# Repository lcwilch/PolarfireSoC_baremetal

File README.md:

# PolarfireSoC_baremetal
Projects for learing Microchip Polarfire SoC using the BeagleV-Fire SBC.
https://www.microchip.com/en-us/products/fpgas-and-plds/system-on-chip-fpgas/polarfire-soc-fpgas
https://www.beagleboard.org/boards/beaglev-fire

# Docs:
MPFS, RISCV documents

# KiCad:
Any PCBs needed to support development (i.e. J-Link to Flashpro JTAG pinout adapter)

# Libero:
MSS Configurator and Libero Projects for configuring MPFS HW

# Schematics:
BeagleV-Fire schematic

# Source:
ESW projects targeting various functionality of the MPFS using U54 core complex

# Debug
Debug utilities, like openocd and fpserver for debuging MPFS with flashpro

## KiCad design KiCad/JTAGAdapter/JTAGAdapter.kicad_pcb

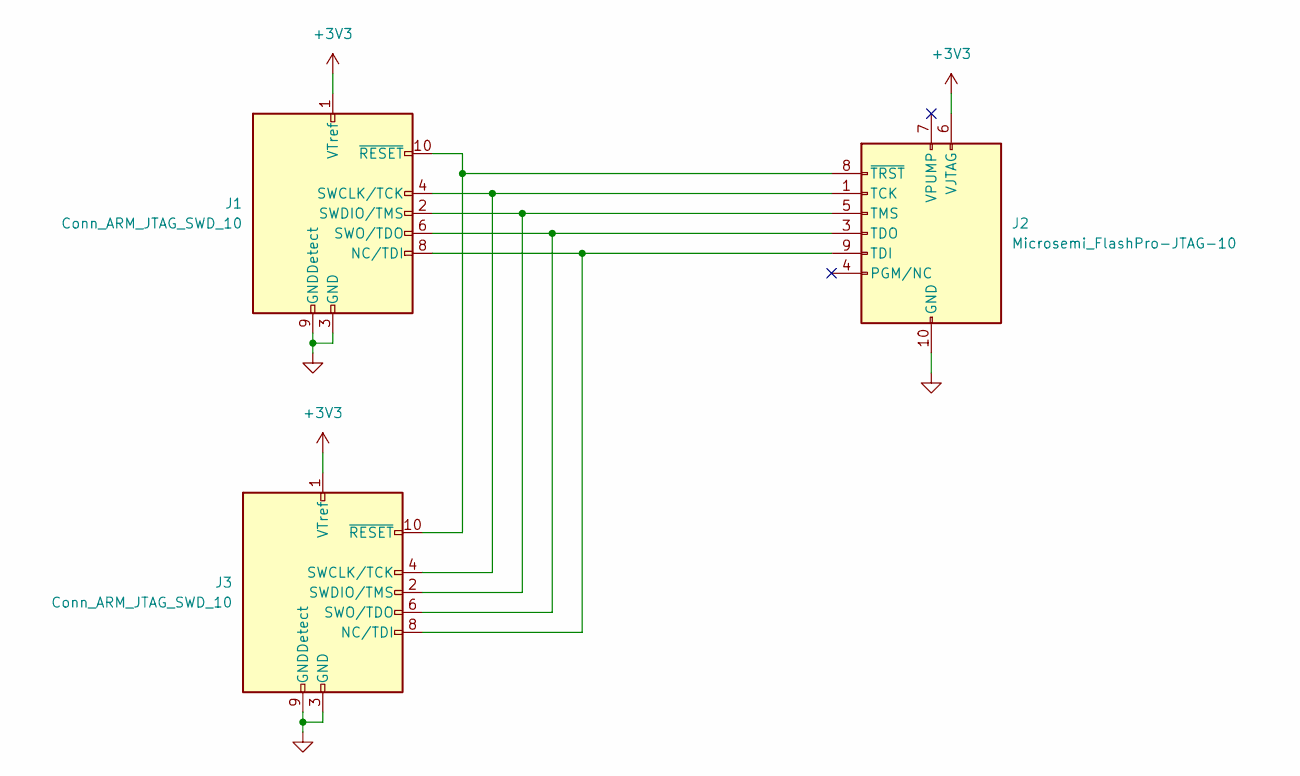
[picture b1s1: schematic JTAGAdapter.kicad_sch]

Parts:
J1: Conn_ARM_JTAG_SWD_10; PinHeader_2x05_P2.54mm_Vertical
J2: Microsemi_FlashPro-JTAG-10; PinHeader_2x05_P2.54mm_Vertical
J3: Conn_ARM_JTAG_SWD_10; PinHeader_2x05_P1.27mm_Vertical

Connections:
+3V3: J1.1 (VTref), J2.6 (VJTAG), J3.1 (VTref)
GND: J1.3 (GND), J1.5 (GND), J1.9 (GNDDetect), J2.2 (GND), J2.10 (GND), J3.3 (GND), J3.5 (GND), J3.9 (GNDDetect)
unnamed: J1.8 (NC/TDI), J2.9 (TDI), J3.8 (NC/TDI)
unnamed: J1.4 (SWCLK/TCK), J2.1 (TCK), J3.4 (SWCLK/TCK)
unnamed: J1.2 (SWDIO/TMS), J2.5 (TMS), J3.2 (SWDIO/TMS)
unnamed: J1.6 (SWO/TDO), J2.3 (TDO), J3.6 (SWO/TDO)
unnamed: J1.10 (~RESET), J2.8 (~TRST), J3.10 (~RESET)

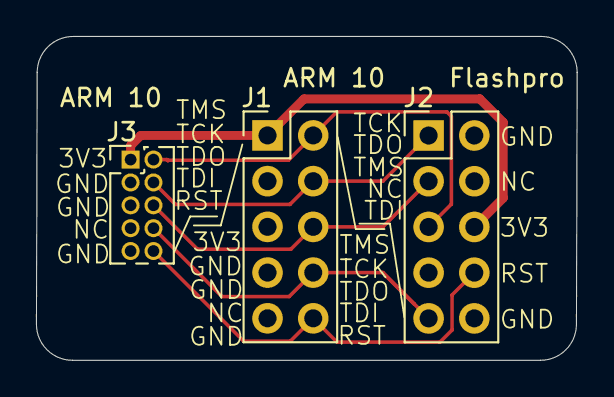
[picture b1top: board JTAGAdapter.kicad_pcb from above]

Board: 2 copper layers, 30.0 x 18.0 mm, 3 parts (0 on the bottom side), 7 nets.

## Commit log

2024-05-11 Added schematics and docs
2024-05-11 Added some readmes and project source directory structure.
2024-05-13 Created MSS config and Libero for eNVM barebones
2024-05-16 Added RISCV docs. eNVM project build completes without errors, but needs work.
2024-05-16 Cleaned up repo
2024-05-17 Added riscv asm manual to docs
2024-05-30 Getting setup on new machine. Change some comments in README.
2024-06-04 Libero blinky example done.
2024-06-17 Segger to Flashpro JTAG adapter created and ordered.
2024-06-22 Grabbed debug tools from Softconsole and put them in Debug dir. Run debug_mpfs.sh for openocd.
2024-06-22 Added .DS_Store to git ignore and removed cached files.
2024-06-22 Removed a debug libero project.
2024-06-22 Debugging setup functional, using OpenOCD and GDB (see README.md in Debug). Created simple statup code to initialize regs and hang forever (see Source/001_MPFS_LIM_hello_world). Able to build, load, 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
2024-06-26 Created new source project to use crt0 to init C runtime and call main. Renamed 001.
2024-06-26 Added some links to READMEs.
2024-06-26 Improved LIM_main.ld to oranize the sections correctly (debugged previous implementation with objdump -x and saw .sdata and .sbss were getting split up.
2024-06-26 Added fill pattern to heap section. Investigated using -nostdlib, but it removes crt0.
